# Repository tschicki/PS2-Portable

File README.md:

# A Custom PlayStation 2 Portable from Scratch

## About this Project
Just like the title says, this is a PlayStation 2 portable designed from scratch. This portable contains presumably world's first custom reverse engineered PS2 mainboard not made by Sony. It is only reusing 6 ICs of an original PS2, salvaged from SCPH-7900x or SCPH-9000x mainboards.

Most PS2 games can be played natively via OPL or NHDDL and the portable also features support for PS1 games via DKWDRV. Its two custom memory card slots are compatible with miniaturized PS2 Memory Cards, SD-Cards (MX4SIO) and a miniaturized SD2PSX.

Development of this project was started in 2022.

## Overview

### Custom PS2 AIO Mainboard
The mainboard was designed from scratch and is based on the SCPH-7900x and SCPH-9000x PS2 revisions. It also includes modern features, like USB-C PD charging and battery management, fully digital video output, I2S speaker and headphone amplifier and a customized boot ROM to boot directly into homebrew.  

#### Details:

- Battery Management:
    - USB C PD charging at 5V/9V/15V
    - Powered from 2S 5000mAh 21700 batteries for a total of 37Wh or about 4.5h of runtime on a single charge
    - Supports charge & play and includes a battery fuel gauge, protector and cell balancing

- Power Management:
    - Custom developed power management featuring modest EE and GS undervolting
    - Soft power button with minimal quiescent current
    - Monitoring to detect short circuits and overcurrent conditions

- Video Output:
    - Custom developed digital video processor based on a Trion T20 FPGA, written from scratch in VHDL
    - Fully digital direct drive of a 5” 480x800p DPI LCD by tapping right into the Graphics Synthesizer 24bit RGB output, replacing the stock PS2 video DAC
    - Features a motion-adaptive deinterlacer, line doubler, bilinear video scaler and OSD
    - Includes support for following resolutions:
        - 512i(256p) x 256, 512i(256p) x 320, 512i(256p) x 384, 512i(256p) x 448, 512i(256p) x 512, 512i(256p) x 640 at 50Hz
        - 448i(240p) x 256, 448i(240p) x 320, 448i(240p) x 384 at, 448i(240p) x 448, 448i(240p) x 512, 448i(240p) x 640 at 60Hz
        - VESA 480x640 at 60Hz

- Audio:
    - Custom I2S headphone and speaker amplifier using LM49450

- System Management:
    - Custom RP2040-based System Controller (SysCon) handling charging, discharging, power on/off, power management and monitoring
    - Custom developed DualShock 2 gamepad emulator running on core 1
        - Developed from scratch
        - Including rumble
        - Support for PS1 games
    - Custom developed configuration menu for changing and displaying various settings:
        - State of charge display (both in menu and via RGB LED)
        - EE temperature display and fan settings
        - Headphone and speaker volume
        - Various video processing settings, LCD brightness
        - Analog stick calibration and inversion
        - Deadzone settings
        - Power monitoring and TTE/TTF
        - And more…
    - SysCon firmware and video processor gateware updatable via drag & drop from USB-C

- Custom PS2 Boot ROM
    - Boots directly into PS2BBL, thanks to the BIOS modifications of Epaminondas – no softmods required

- Additional Features:
    - Fully functional PS2 RTC, enabled by an always-on standby rail

### Mechanical Assembly

The whole mechanical assembly was designed from scratch for FDM printing. The design goal was to make it as ergonomic as possible, while keeping the overall appearance simple and minimalistic.
The assembly is split into an outer shell and an inner assembly called 'skeleton' in an attempt to make assembly & disassembly easier and to allow easy shell replacements. Another priority for me was to use threaded inserts for all screws and to have easily replaceable non-soldered batteries.

#### Details:

- Gamepads
    - Custom designed & modular gamepad subassemblies that connect to the mainboard via I2C for best flexibility
    - PSVITA 2000 face buttons
    - 3.3V Nintendo Switch hall effect analog sticks
    - Rumble support: Coin-style rumble motors
    - Custom developed trigger mechanism using living hinges

- Cooling:
    - Custom designed aluminium heatsink covering the whole mainboard for maximum mechanical rigidity
    - Nintendo switch lite fan with configurable linear fan curve

- Interfaces:
    - Two fully accessible memory card slots, miniaturized by reusing SD card sockets
        - Natively compatible with MX4SIO, a custom reverse engineered PS2 memory card and a custom form factor SD2PSX 'uSD2PSX'
    - One USB A connector of the PS2, for using original accessories or USB sticks (DKWDRV)
    - Stereo headphone jack
    - USB-C connector for charging and SysCon firmware update

- Video and Audio
    - Stereo Nintendo Switch OLED speakers
    - 5" DPI LCD covered by a Nintendo 3DS XL glass screen lens

## Accessories
To further enhance the user experience, some more or less optional accessories were designed. 
- A *uSD2PSX* memory card in SD-Card format for running backups and saving games. Can also be unplugged to play on multiple consoles / portables, and is compatible for use on a stock console using a modified MX4SIO memory card. The best way to play games on the PS2 portable, and pretty much mandatory.
- A stand to place the portable while charging and when not in use.
- A travel case to protect the portable on-the-go.
- A reverse engineered PS2 memory card for saving games. Same form factor and interface as the uSD2PSX, but less useful. Don't bother with this and build the uSD2PSX instead.

## How to Build
I would highly recommend **not** to build one, even if you know what you are getting yourself into. If you're still not convinced to stop here, you can find the project documentation in the [documentation](https://github.com/tschicki/PS2-Portable/tree/main/Documentation) folder. It's best to read all the docs before you decide to continue.

You will need a lot of equipment and comprehensive electronics, soldering, troubleshooting and preferably also programming skills to have a chance of getting the custom PS2 mainboard to boot.

There is a [worklog](https://bitbuilt.net/forums/threads/some-ps2-project.5433/) of the whole project on BitBuilt, you might find some additional information there.

### Electronics
All custom PCBs, their Gerbers and their BOM can be found in the respective project under the [Electronics](https://github.com/tschicki/PS2-Portable/tree/main/Electronics) folder. All PCBs come from JLCPCB.

### Mechanics
All custom designed mechanical parts can be found under [Solidworks](https://github.com/tschicki/PS2-Portable/tree/main/Solidworks). If you would like to edit them, they were all designed using SolidWorks Maker. Otherwise, the STEP and STL exports can be found under [Output](https://github.com/tschicki/PS2-Portable/tree/main/Solidworks/Output).  
The housing parts were designed to be FDM printed, the CNC heatsink can be ordered from JLCCNC.

### Firmware & Gateware
The source files of the left & right gamepad firmware can be found [here](https://github.com/tschicki/PS2-Portable/tree/main/SysCon%20Firmware/PS2_Gamepad_02).  
The SysCon firmware can be found [here](https://github.com/tschicki/PS2-Portable/tree/main/SysCon%20Firmware/SysCon_FW).  
The Trion T20 gateware can be found [here](https://github.com/tschicki/PS2-Portable/tree/main/SysCon%20Firmware/SysCon_FW/ps2_video_processor).  

In order to obtain the required firmware, you need to compile it yourself. See the [documentation](https://github.com/tschicki/PS2-Portable/blob/main/Documentation/Part%2010_Development%20and%20Debugging.md) for that.

### Bill of Materials
The bill of materials for the mechanical assembly can be found [here](https://github.com/tschicki/PS2-Portable/blob/main/Documentation/Part%200_Mechanical%20BOM.md). The electrical BOM for each PCBA is in the [Electronics](https://github.com/tschicki/PS2-Portable/tree/main/Electronics) folder.

### Assembly Instructions
Check the [documentation](https://github.com/tschicki/PS2-Portable/tree/main/Documentation) folder. I tried to structure the sequence of documents so that it can guide you along for your build.

## Special Thanks
Thanks to the BitBuilt community for reading and commenting the worklog, it really helped to keep the motivation up! And special thanks to:
- Mister M and Gman for releasing their PS2 mainboard scans – without them this project would’ve taken much longer!
- Epaminondas for his amazing work on the custom PS2 BIOS. Seriously, you rock!
- Stuckpixel for helping out with converting the SPI part of the gamepad emulator to PIO. It’s much more reliable now!
- wisi and mixa232323 for guiding me in the right direction with all the boot ROM shenanigans
- StonedEdge and thedrew for their various suggestions and tips along the way
- All the awesome people working on the SD2PSX, neutrino and NHDDL! It's incredible to see how far the PS2 homebrew scene has come in the last couple of years!

## Known Bugs and Anomalies
This is a hobby project, so the end result will never be flawless. The design has seen hundreds of hours of playtesting, where following anomalies were discovered:
- The PS2 RTC drifts by about 7s a day, this could most likely be solved by selecting a different 32kHz crystal or by tweaking the load capacitors. However, the characteristics of the original crystal and the Mechacon's oscillator circuits are unknown.
- Games with static and permanently flickering elements can cause image retention on the LCD. I only noticed this on one game so far - Castlevania: Symphony of the Night, where certain HUD elements flicker. It is not recommended to play such games to prevent damage to the LCD.

## License
All firmware, gateware and hardware in this repository is licensed under the [MIT License](LICENSE).

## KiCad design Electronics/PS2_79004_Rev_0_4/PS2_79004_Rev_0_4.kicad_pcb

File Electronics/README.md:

# PCB Outputs

This directory contains all the PCB projects. You will find the Gerber files in the respective *Gerber/* folders. The BOM is in ibom format and can be found in the *BOM/* folders where applicable. For very simple PCBs like the gamepad flex PCBs you will find the needed components in Part 5 of the project documentation.

If you need the BOM in CSV format, you can open the ibom files and export the content as CSV.

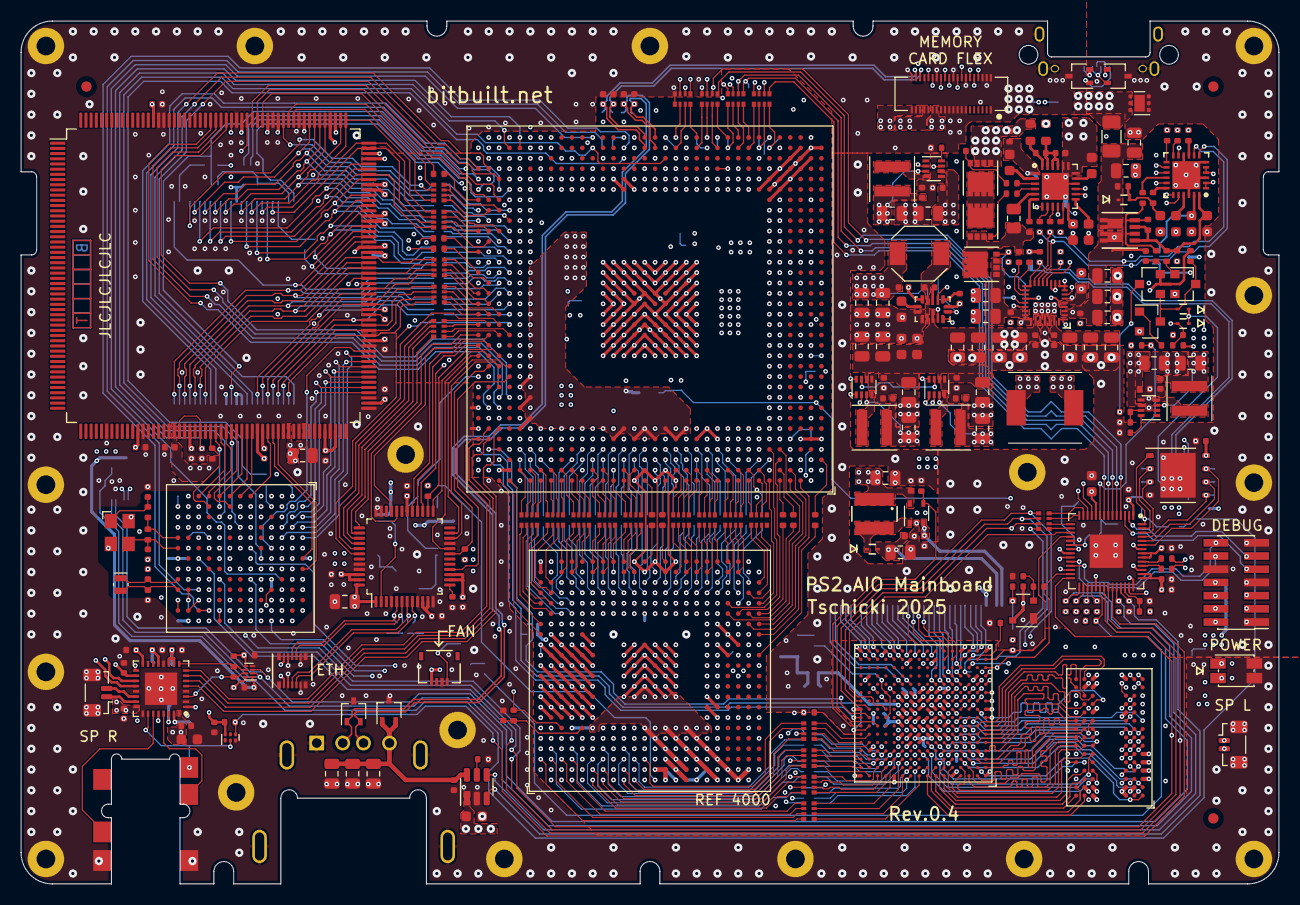
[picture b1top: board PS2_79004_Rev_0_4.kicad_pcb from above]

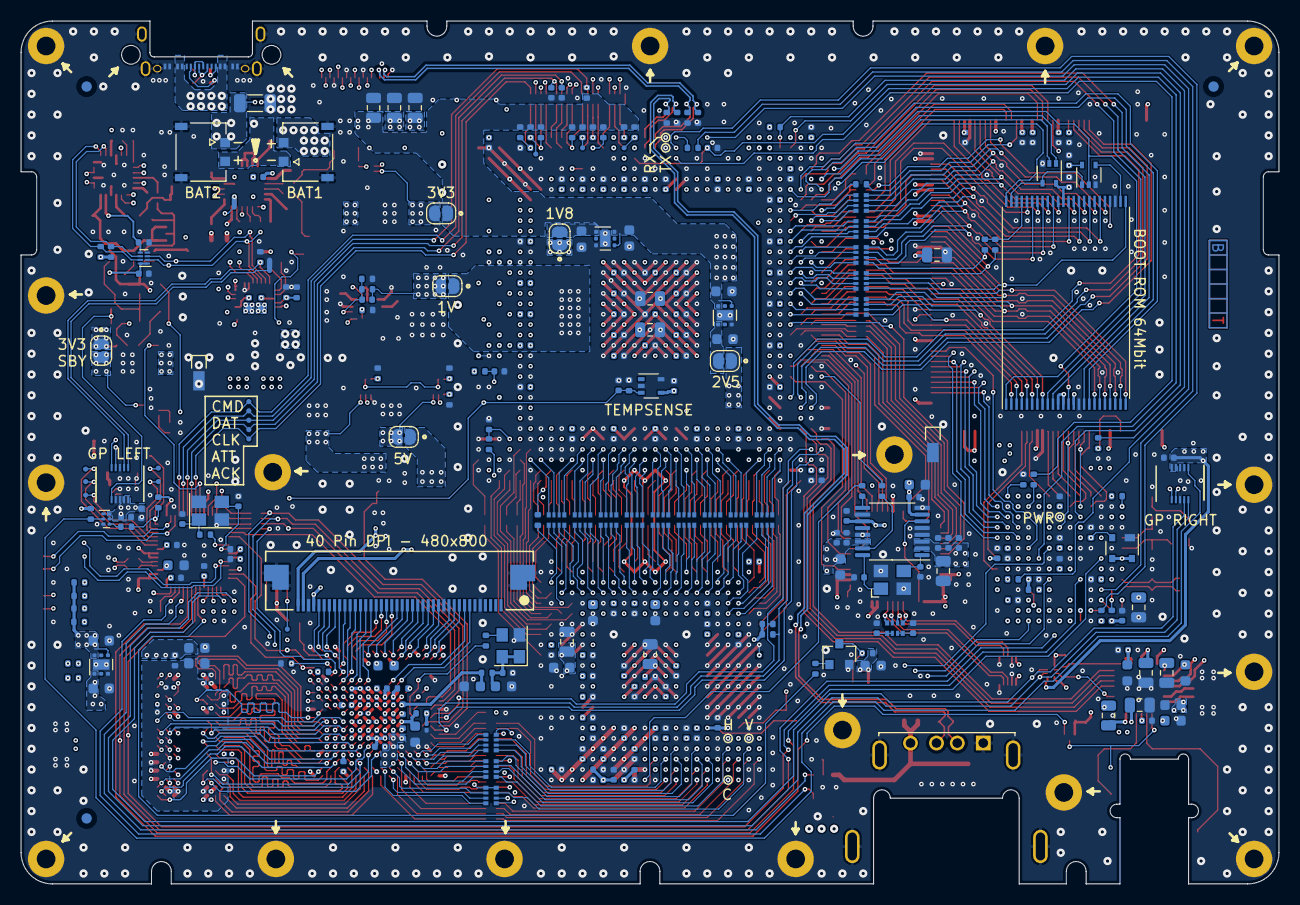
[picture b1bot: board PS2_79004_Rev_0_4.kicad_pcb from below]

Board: 6 copper layers, 121.0 x 83.0 mm, 770 parts (488 on the bottom side), 807 nets.

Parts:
C201, C202, C1402, C2002, C2003, C2105, C2106, C2112, C2504: 2u2; C_0805_2012Metric
C203, C204, C205, C206, C605, C616, C806, C809, C2107, C2114, C2115, C2118, C2119, C2202, C2205, C2208: 1u; C_0603_1608Metric
C207, C208, C306, C309, C314, C318, C325, C328, C401, C510, C511, C512, C513, C516, C517, C518, C519, C532, C601, C602, C606, C607, C608, C609, C610, C611, C612, C613, C614, C615, C801, C805, C810, C901, C905, C906, C907, C908, C909, C910, C911, C912, C913, C914, C916, C917, C918, C919, C920, C921, C922, C923, C924, C925, C926, C927, C928, C929, C930, C931, C932, C933, C934, C935, C936, C937, C938, C939, C944, C1301, C1401, C1403, C1404, C1405, C1406, C1407, C1408, C1409, C1503, C1504, C1507, C1601, C1602, C1701, C1702, C1802, C1803, C1804, C1805, C1806, C1807, C1808, C1809, C1810, C1811, C1813, C1814, C1815, C1816, C1817, C1818, C2001, C2004, C2005, C2006, C2007, C2008, C2101, C2102, C2104, C2108, C2109, C2110, C2111, C2113, C2116, C2117, C2201, C2203, C2204, C2206, C2207, C2209, C2210, C2213, C2215, C2216, C2217, C2218, C2219, C2220, C2221, C2222, C2223, C2224, C2225, C2226, C2227, C2229, C2230, C2231, C2232, C2233, C2234, C2235, C2236, C2237, C2502, C2903, C3005, C3006: 100n; C_0402_1005Metric
C301, C302, C303, C304, C305, C307, C316, C319, C320, C321, C322, C323, C501, C502, C1801, C1812, C2103, C2501: 10u; C_0805_2012Metric
C308, C503, C506, C509, C528, C529, C530, C531, C534, C535, C538, C2601, C2608, C2801, C2814, C3004: 4u7; C_0603_1608Metric
C310, C311: 47n; C_0402_1005Metric
C312, C315, C317, C324, C2901, C2902: 470n; C_0603_1608Metric
C313, C803, C808, C811, C1303, C2212, C2228, C2301, C2503: 1n; C_0402_1005Metric
C326, C327, C525, C807, C902, C903, C904, C915, C940: 10n; C_0402_1005Metric
C504, C505, C507, C508, C521, C522, C523, C524, C533, C536, C537, C942, C943, C2211, C2214, C3001, C3002, C3003: 22u; C_0805_2012Metric
C514, C2602, C2618, C2625, C2626, C2627, C2628: 220n; C_0402_1005Metric
C515: 22n; C_0402_1005Metric
C520: 270p; C_0402_1005Metric
C526, C527: 47u; C_0805_2012Metric
C603, C604, C1501, C1502, C1505, C1506: 15p; C_0402_1005Metric
C802, C804, C1302: 5p; C_0402_1005Metric
C941, C2401, C2402, C2403, C2404, C2405, C2406, C2407: 100p; C_0402_1005Metric
C2603, C2604, C2605, C2606, C2607, C2609, C2610, C2611, C2612, C2613, C2614, C2615, C2616, C2617, C2619, C2620, C2621, C2622, C2623, C2624, C2802, C2803, C2804, C2805, C2806, C2807, C2808, C2809, C2810, C2811, C2812, C2813: 100n; C_0201_0603Metric
D201, D202, D3001, D3002: ESDA25W; SOT-323_SC-70
D203, D401, D402, D2501: D_Schottky; SOD-923_0P6X0P85_ONS
D1501: Power LED; LED_Lite-ON_LTST-C155
F201: Fuse; Fuse_1206_3216Metric
FB2601, FB2801, FB2901: 33R @ 100MHz; R_0402_1005Metric
FID3001, FID3002, FID3003, FID3004, FID3005, FID3006: Fiducial; Fiducial_1mm_Mask2mm
J301: BAT1; MOLEX_2082940020_2pin
J302: BAT2; MOLEX_2082940020_2pin
J2101: LEFT SPEAKER; JST_SUR_BM02B-SURS-TF_1x02-1MP_P0.80mm_Vertical
J2102: RIGHT SPEAKER; JST_SUR_BM02B-SURS-TF_1x02-1MP_P0.80mm_Vertical
J2103: SJ-43504-SMT-TR; CUI_SJ-43504-SMT-TR
J2501: Conn_01x40_MountingPin; CONN_62684402100ALF_AMP
J3001: EXPANSION HDR; DF40C-40DS-0.4V
J3002: ETH; DF40C-10DP-0.4V51_HIR
J3003: USB_A; PS2_USB_mid_mount
J3004: GAMEPAD LEFT; DF40C-10DS-0.4V51_HIR
J3005: GAMEPAD RIGHT; DF40C-10DS-0.4V51_HIR
J3006: Debug; FTSH-107-01-F-DV-K-P-TR
J3007: 2328702-4; TE_2328702-4
JP501, JP502, JP503, JP504, JP505, JP506: Jumper_2_Bridged; SolderJumper-2_P1.3mm_Open_RoundedPad1.0x1.5mm
L301: 1uH; L_TDK_SPM6530
L501, L502, L503, L504: 2u2; L_Coilcraft_XGL4020
L505: 1u; SPM5030T-1R0M
L2501: 4u7; IND_TAIYO_NRS4012_TAY
NT301, NT302: NetTie_2; NetTie-2_SMD_Pad0.5mm
P201: CX90MW6-16P; CX90_632x232_HIR
Q201: Q_SI7223DN; PowerPAK1212-8_VIS
Q301, Q302, Q303: CSD17575Q3; CSD17308Q3
Q401, Q402, Q601: DMN67D8L; SOT-23
Q403: BSS84AK; SOT-23
R201, R1701, R1702: 560R; R_0402_1005Metric
R202, R205, R311, R313, R406, R604, R606, R614, R616, R1304, R1305, R1307, R1504, R1505, R1507, R1508, R1510, R2001, R2307, R2401, R2402, R2403, R2404, R2405, R2406, R2408, R2409, R2411, R2412: 1k; R_0402_1005Metric
R203, R206, R207, R211, R309, R401, R404, R507, R607, R610, R2101: 100k; R_0402_1005Metric
R204, R509, R2407, R2410, R2413, R2414: 15k; R_0402_1005Metric
R208, R209, R301, R601, R608, R609, R611, R612, R613, R2103, R2104: 2k2; R_0402_1005Metric
R210, R306: 100R; R_0402_1005Metric
R302, R303, R2902: 12k; R_0402_1005Metric
R304, R305, R314, R315, R1301, R1302, R1303, R1306, R1509, R2301, R2302, R2303, R2304, R2305, R2306, R2308: 68R; R_0402_1005Metric
R307: 30k; R_0402_1005Metric
R308: 5k23; R_0402_1005Metric
R310: 270R; R_0805_2012Metric
R312: 0R01; R_1206_3216Metric
R316: 10R; R_0402_1005Metric
R317, R318: 68R; R_0603_1608Metric
R402, R403, R405, R407, R501, R508, R605, R615, R1201, R1202, R1501, R1502, R1503, R1514, R1601, R2102, R2501, R2701, R2702, R2703, R2704, R2705, R2706, R2707, R2708, R2709, R2710, R2711: 10k; R_0402_1005Metric
R502, R503, R504, R505: 42k2; R_0402_1005Metric
R506: 6k8; R_0402_1005Metric
R510, R1512, R1515: 45k3; R_0402_1005Metric
R602, R603, R801, R802, R1506, R2901: 22R; R_0402_1005Metric
R1511: 1M; R_0402_1005Metric
R1513, R2002: 1K5; R_0402_1005Metric
R2003: 1K2; R_0402_1005Metric
R2502: 5R6; R_0402_1005Metric
RN601, RN1301, RN1302, RN1303, RN1304, RN1305, RN1306, RN1307, RN1308, RN1309, RN2001, RN2301, RN2302, RN2303, RN2304, RN2305, RN2306, RN2307, RN2308, RN2309, RN2310, RN2311, RN2312, RN2313, RN2314, RN2315, RN2316, RN2317, RN2318, RN2319, RN2320, RN2321, RN2322, RN2323, RN2324, RN2325, RN2401, RN2402, RN2403, RN2404: 68R; R_Array_Convex_4x0402
RN2002: 51R; R_Array_Convex_4x0402
TP201, TP202, TP203, TP204, TP205, TP206, TP301, TP302, TP303, TP304, TP305, TP306, TP601, TP602, TP603, TP604, TP605, TP606, TP607, TP608, TP1101, TP1301, TP1302, TP1303, TP1304, TP1305, TP1306, TP1307, TP1308, TP1309, TP1310, TP1311, TP1312, TP1313, TP1314, TP1315, TP1316, TP1317, TP1318, TP1319, TP1320, TP1321, TP1322, TP1323, TP1324, TP1325, TP1326, TP1327, TP1328, TP1329, TP1501, TP1502, TP1503, TP1504, TP1505, TP1506, TP1507, TP1508, TP1509, TP1510, TP1511, TP1512, TP1513, TP1514, TP1515, TP1516, TP1517, TP1518, TP1519, TP1520, TP1521, TP1522, TP1523, TP1524, TP1525, TP1526, TP1527, TP1528, TP1529, TP1530, TP1531, TP1532, TP1533, TP1534, TP1535, TP1536, TP1537, TP1538, TP1539, TP1540, TP1541, TP1542, TP1543, TP1544, TP1545, TP1546, TP1547, TP1548, TP1701, TP1702, TP1703, TP1704, TP1901, TP2301, TP2302, TP2303, TP2304, TP2305, TP2306, TP2307, TP2308, TP2309, TP2310, TP2311, TP2312, TP2313, TP2314, TP2315, TP2316, TP2317, TP2318, TP2319, TP2320, TP2321, TP2322, TP2323, TP2324, TP2325, TP2326, TP2327, TP2328, TP2329, TP2330, TP2331, TP2332, TP2333, TP2334, TP2335, TP2401, TP2402, TP2403, TP2404, TP2405, TP2406, TP2407, TP2408, TP2409, TP2410, TP2411, TP2412, TP2701, TP2702, TP2703, TP2704, TP2705, TP2706, TP2707, TP2708, TP2709, TP2901, TP2902, TP2903, TP2904, TP2905, TP2906: Solder_Point; Solder_Point_127
TP3001, TP3002, TP3003, TP3004, TP3005, TP3006, TP3007, TP3008, TP3009, TP3010, TP3011, TP3012, TP3013, TP3014, TP3015, TP3016, TP3017: Solder_Point; mounting_hole_1.6mm
TP3018, TP3019: Solder_Point; TE_1551576-5
U201: TVS2200DRV; WSON-6-1EP_2x2mm_P0.65mm_EP1x1.6mm
U202: STUSB4500; QFN-24_EP_4x4_Pitch0.5mm
U203, U2101: TXS0102DQE; X2SON-8_1.4x1mm_P0.35mm
U301: BQ25792B; BQ25792RQMR
U302: MAX17320; TQFN-24-1EP_4x4mm_P0.5mm_EP2.6x2.6mm
U501: MPQ8626GD; MPQ8626GD-Z
U502, U503, U504, U505: TPS629210; SOT-583
U506: AP22653A; SOT-23-6
U507: TLV75525PDRV; WSON-6-1EP_2x2mm_P0.65mm_EP1x1.6mm
U508, U509: TLV75518PDRV; WSON-6-1EP_2x2mm_P0.65mm_EP1x1.6mm
U601, U2102: 74LVC1G07; Texas_USON-6_1x1.45mm_P0.5mm_SMD
U602: W25Q128JVPIQ; WSON-8-1EP_6x5mm_P1.27mm_EP3.4x4.3mm
U603: RP2040; QFN-56-1EP_7x7mm_P0.4mm_EP3.2x3.2mm
U801: 627G04LF; TSSOP-16_4.4x5mm_P0.65mm
U901: CXD2976GB; PS2_CXD2976GB_35.0x35.0mm_P1.0mm
U1401: CXR726080; BGA-169_14.0x14.0mm_Layout13x13_P1.0mm
U1501, U2701: APX811-31UG; SOT-143
U1601: LM20BIM7; SOT-353_SC-70-5
U1701, U1702: 74LVC1G08; SOT-353_SC-70-5
U1703: S29JL064J55TFI000; TSOP-I-48_18.4x12mm_P0.5mm
U1801: CXD3098AQ; PS2_CXD3098AQ_208_28x28mm_P0.5mm
U2001: BCM5241; LQFP-48_7x7mm_P0.5mm
U2103: LM49450; WQFN-32-1EP_5x5mm_P0.5mm_EP3.1x3.1mm
U2201: CXD2980; PS2_CXD2980CGB_23.0x23.0mm_P1.0mm
U2501: TPS92360; SOT-353_SC-70-5
U2601: T20F256I4; BGA-256_14.0x14.0mm_Layout16x16_P0.8mm_Ball0.45mm_Pad0.32mm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
U2801: IS45S32400F; BGA-90_8.0x13.0mm_Layout2x3x15_P0.8mm
X2901: ASE-50MHz; Oscillator_SMD_Abracon_ASE-4Pin_3.2x2.5mm
Y601: 12MHz; Crystal_SMD_3225-4Pin_3.2x2.5mm
Y801: 18.432MHz; Crystal_SMD_3225-4Pin_3.2x2.5mm
Y1501: 32.768kHz; Crystal_SMD_MicroCrystal_CM9V-T1A-2Pin_1.6x1.0mm
Y1502: 16,934MHz; Crystal_SMD_3225-4Pin_3.2x2.5mm

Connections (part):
1V2_T20: C516.1, C521.1, C2601.1, C2602.1, C2603.1, C2604.1, C2605.1, C2606.1, C2607.1, C2609.1, C2611.1, FB2601.1, L501.2, U502.3 (VOS), U2601.E9 (VCC), U2601.F8 (VCC), U2601.F9 (VCC), U2601.J6 (VCC), U2601.J7 (VCC), U2601.K9 (VCC)
1V8_PS2: C809.1, C810.1, C811.1, C906.1, C908.1, C910.1, C912.1, C915.1, C918.1, C921.1, C923.1, C925.1, C927.1, C929.1, C1407.2, C1408.2, C1409.2, C1812.1, C1813.1, C1814.1, C1815.1, C1816.1, C1817.1, C1818.1, C2221.1, C2223.1, C2225.1, C2227.1, C2229.1, C2230.1, C2231.1, C2232.1, C2233.1, C2234.1, C2235.1, C2236.1, C2237.1, JP506.2 (B), U801.7 (1V8), U801.11 (1V8), U901.AA5 (1V8), U901.AB6 (1V8), U901.AB30 (1V8), U901.AC5 (1V8), U901.AC29 (1V8), U901.AD6 (1V8), U901.AD30 (1V8), U901.AE5 (1V8), U901.AE29 (1V8), U901.AF6 (1V8), U901.AF30 (1V8), U901.AG5 (1V8), U901.AG29 (1V8), U901.AH30 (1V8), U901.AJ21 (1V8), U901.AJ23 (1V8), U901.AJ25 (1V8), U901.AJ27 (1V8), U901.AJ29 (1V8), U901.AK22 (1V8), U901.AK24 (1V8), U901.AK26 (1V8), U901.AK28 (1V8), U901.AK30 (1V8), U901.AL31 (1V8), U901.AM32 (1V8), U901.AN33 (1V8), U901.B2 (1V8), U901.C3 (1V8), U901.D4 (1V8), U901.E5 (1V8), U901.E7 (1V8), U901.E9 (1V8), U901.E11 (1V8), U901.E13 (1V8), U901.F6 (1V8), U901.F8 (1V8), U901.F10 (1V8), U901.F12 (1V8), U901.G5 (1V8), U901.H6 (1V8)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
1V8_T20: C538.1, C2616.1, C2623.1, C2628.1, U509.1 (OUT), U2601.E10 (VCCIO3A_3B_3C), U2601.F10 (VCCIO3A_3B_3C), U2601.F11 (VCCIO3A_3B_3C)
1V_PS2: C913.1, C916.1, C919.1, C922.1, C924.1, C926.1, C928.1, C930.1, C931.1, C932.1, C933.1, C934.1, C935.1, C936.1, C937.1, C938.1, C939.1, C940.1, C941.1, C942.1, C943.1, C944.1, C2201.1, C2202.1, C2204.1, C2205.1, C2207.1, C2208.1, C2210.1, C2211.1, C2213.1, C2214.1, C2216.1, C2218.1, C2220.1, C2222.1, C2224.1, C2226.1, C2228.1, JP501.2 (B), U901.AA14 (1V25), U901.AA16 (1V25), U901.AA18 (1V25), U901.AA20 (1V25), U901.AA22 (1V25), U901.AB13 (1V25), U901.AB15 (1V25), U901.AB17 (1V25), U901.AB19 (1V25), U901.AB21 (1V25), U901.AJ9 (1V25), U901.AJ11 (1V25), U901.AJ13 (1V25), U901.AJ15 (1V25), U901.AJ17 (1V25), U901.AJ19 (1V25), U901.AK8 (1V25), U901.AK10 (1V25), U901.AK12 (1V25), U901.AK14 (1V25), U901.AK16 (1V25), U901.AK18 (1V25), U901.AK20 (1V25), U901.B34 (1V25), U901.N14 (1V25), U901.N16 (1V25), U901.N18 (1V25), U901.N20 (1V25), U901.N22 (1V25), U901.P13 (1V25), U901.P15 (1V25), U901.P17 (1V25), U901.P19 (1V25), U901.P21 (1V25), U901.R14 (1V25), U901.R16 (1V25), U901.R18 (1V25), U901.R20 (1V25), U901.R22 (1V25), U901.T13 (1V25), U901.T15 (1V25)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
2V5_PS2: C914.1, C917.1, C920.1, C2116.1, C2117.1, C2118.1, C2119.1, C2203.1, C2206.1, C2209.1, C2212.1, JP505.2 (B), U901.AP2 (2V5), U901.AP33 (2V5), U901.B33 (2V5), U2103.28 (HPVDD), U2103.32 (CPVDD), U2201.A21 (2V5), U2201.T1 (2V5)
3V3_PS2: C529.1, C530.1, C801.1, C803.1, C805.1, C806.1, C807.1, C808.1, C901.1, C902.1, C903.1, C904.1, C905.1, C907.1, C909.1, C911.1, C1403.1, C1404.1, C1405.1, C1406.1, C1507.1, C1601.1, C1701.1, C1702.1, C1801.1, C1802.1, C1803.1, C1804.1, C1805.1, C1806.1, C1807.1, C1808.1, C1809.1, C1810.1, C1811.1, C2002.1, C2004.1, C2005.1, C2006.1, C2102.1, C2107.1, C2108.1, C2109.1, C2215.1, C2217.1, C2219.1, C3003.1, J3001.27, J3001.29, J3002.9, J3002.10, JP504.2 (B), R1201.1, R1202.1, R1304.2, R1501.1, R1503.1, R1512.1, R1515.1, R2001.1, R2002.1, R2101.2, R2102.1, R2103.1, R2104.1, R2401.1, R2402.1, R2403.1, R2404.1, R2405.1, R2406.1, R2408.1, R2409.1, R2411.1, R2412.1, U507.4 (EN), U507.6 (IN), U508.4 (EN), U508.6 (IN), U801.2 (3V5), U801.3 (3V5)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
3V3_SBY: C208.2, C601.1, C602.1, C608.1, C609.1, C610.1, C611.1, C612.1, C614.1, C615.1, C616.1, C2101.2, C3002.1, C3005.1, C3006.1, J3001.31, J3001.33, J3004.8, J3004.10, J3005.8, J3005.10, JP503.2 (B), R208.1, R209.1, R301.2, R407.1, R601.1, R605.1, R608.1, R609.1, R610.2, R611.1, R612.1, R613.1, U203.1 (VCCA), U203.8 (VCCB), U601.6 (VCC), U602.8 (VCC), U603.1 (IOVDD), U603.10 (IOVDD), U603.22 (IOVDD), U603.33 (IOVDD), U603.42 (IOVDD), U603.43 (ADC_AVDD), U603.44 (VREG_IN), U603.48 (USB_VDD), U603.49 (IOVDD), U2101.1 (VCCA)
3V3_T20: C517.1, C522.1, C531.1, C2612.1, C2613.1, C2614.1, C2615.1, C2617.1, C2618.1, C2619.1, C2620.1, C2621.1, C2622.1, C2624.1, C2625.1, C2626.1, C2627.1, C2801.1, C2802.1, C2803.1, C2804.1, C2805.1, C2901.1, FB2801.1, FB2901.1, J2501.37, JP504.1 (A), L502.2, R2702.1, R2703.1, R2704.2, R2705.2, R2706.2, R2707.2, R2708.2, R2711.1, U503.3 (VOS), U509.4 (EN), U509.6 (IN), U2601.F6 (VCCIO1D_1E), U2601.G6 (VCCIO1D_1E), U2601.H6 (VCCIO1B_1C), U2601.H7 (VCCIO1B_1C), U2601.J10 (VCCIO3D_3E), U2601.J11 (VCCIO3D_3E), U2601.K6 (VCCIO1A), U2601.L6 (VCCIO4B), U2601.L7 (VCCIO4B), U2601.L10 (VCCIO4A), U2601.L11 (VCCIO4A), U2701.4 (VCC), U2801.A7 (VDD), U2801.F9 (VDD), U2801.L7 (VDD), U2801.R7 (VDD)
5V: C528.1, C2110.1, C2111.1, C2113.1, C2114.1, C2115.1, C2501.2, C2502.1, C3001.1, C3004.1, J3001.35, J3001.37, J3001.39, J3007.1, JP502.2 (B), L2501.1, R615.1, U506.1 (IN), U2103.16 (VDD), U2103.18 (LSVDD), U2103.24 (LSVDD), U2501.5 (VIN)
5V_USB: C532.1, C533.1, C536.1, C537.1, D3001.1 (K), D3001.2 (K), J3003.1 (VBUS), U506.6 (OUT)
+1V1: C605.1, C606.1, C607.1, U603.23 (DVDD), U603.45 (VREG_VOUT), U603.50 (DVDD)
/Battery Management/BAT_CENT: J301.1, J302.2, R318.2
/Battery Management/BAT_POS: C328.1, J301.2, Q303.1 (S), Q303.2 (S), Q303.3 (S), R316.2, R317.2
/Battery Management/BQ_BAT: C318.2, C320.2, C322.2, Q301.1 (S), Q301.2 (S), Q301.3 (S), U301.22 (BAT), U301.23 (BAT)
/Battery Management/ILIM: R309.1, U301.17 (ILIM_HIZ)
/Battery Management/PROG: R302.2, R303.2, U301.20 (PROG)
/Battery Management/REGN: C308.2, R308.2, R309.2, U301.5 (REGN)
/Battery Management/SW1: C310.2, L301.1, U301.28 (SW1)
/Battery Management/SW2: C311.2, L301.2, U301.26 (SW2)
/Battery Management/SYS_I2C_SCL: R304.1, R612.2, U203.2 (A1), U301.14 (SCL), U603.32 (GPIO21)
/Battery Management/SYS_I2C_SDA: R305.1, R611.2, U203.3 (A2), U301.15 (SDA), U603.31 (GPIO20)
/Battery Management/VBUS: C207.2, C302.2, C304.2, C307.2, C309.2, Q201.7 (D), Q201.8 (G), R205.2, U301.2 (VBUS), U301.3 (VBUS), U301.8 (VAC2), U301.9 (VAC1)
/Battery Management/VPACK+: Q301.5-8 (D), Q302.1 (S), Q302.2 (S), Q302.3 (S), R306.2, R310.1, R311.2
/Battery Management/VSYS: C314.2, C316.2, C319.2, C321.2, C323.2, C501.1, C502.1, C504.1, C505.1, C506.1, C507.1, C508.1, C509.1, C510.1, C511.1, C512.1, C513.1, Q403.2 (S), R403.2, U301.25 (SYS), U501.3 (VIN), U502.6 (VIN), U503.6 (VIN), U504.6 (VIN), U505.6 (VIN)
/Battery Management/~CHRG_EN: R301.1, U301.13 (~CE), U603.12 (GPIO9)
/Connectors/MC1_ACK: J3001.32, RN2401.2 (R2.1)
/Connectors/MC1_ATT: J3001.26, RN2401.4 (R4.1)
/Connectors/MC1_CLK: J3001.30, RN2401.3 (R3.1)
/Connectors/MC1_CMD: J3001.24, RN2402.3 (R3.1)
/Connectors/MC1_DAT: J3001.22, RN2402.4 (R4.1)
/Connectors/MC2_ACK: J3001.18, RN2404.3 (R3.1)
/Connectors/MC2_ATT: J3001.12, RN2403.1 (R1.1)
/Connectors/MC2_CLK: J3001.16, RN2404.4 (R4.1)
/Connectors/MC2_CMD: J3001.10, RN2403.2 (R2.1)
/Connectors/MC2_DAT: J3001.8, RN2403.3 (R3.1)
/Connectors/RD+: J3002.3, RN2002.8 (R1.2), U2001.8 (RD+)
/Connectors/RD-: J3002.5, RN2002.7 (R2.2), U2001.7 (RD-)
/Connectors/SPI_SS: J3006.5, R2701.1, U2601.P3 (GPIOL_00_SS_N)
/Connectors/SYS_FAN_PWM: J3007.4, Q601.3 (D), R615.2
/Connectors/SYS_SWCLK: J3006.12, U603.24 (SWCLK)
/Connectors/SYS_SWDIO: J3006.14, U603.25 (SWD)
/Connectors/SYS_UART_RX: J3006.9, U603.3 (GPIO1)
/Connectors/SYS_UART_TX: J3006.11, U603.2 (GPIO0)
/Connectors/TCK: J3006.4, R2706.1, U2601.M2 (TCK)
/Connectors/TD+: J3002.6, RN2002.5 (R4.2), U2001.5 (TD+)
/Connectors/TD-: J3002.4, RN2002.6 (R3.2), U2001.6 (TD-)
/Connectors/TDI: J3006.8, R2704.1, U2601.K5 (TDI)
/Connectors/TDO: J3006.6, R2705.1, U2601.L5 (TDO)
/Connectors/TMS: J3006.2, R2707.1, U2601.M1 (TMS)
/Connectors/USB1_DN: C2406.1, D3002.2 (K), J3003.2 (D-), R2413.1, U901.AN17 (USB1_D-)
/Connectors/USB1_DP: C2407.1, D3002.1 (K), J3003.3 (D+), R2414.1, U901.AP17 (USB1_D+)
/Connectors/USB2_DN: C2404.1, J3001.38, R2407.1, U901.AN18 (USB2_D-)
/Connectors/USB2_DP: C2405.1, J3001.36, R2410.1, U901.AP18 (USB2_D+)
/Connectors/~SYSCON_BOOTSEL: J3005.2, R601.2, U601.2
/PS2_REG_EN: R607.1, U501.5 (EN), U502.7 (EN), U503.7 (EN), U504.7 (EN), U506.3 (EN), U603.39 (GPIO27_ADC1)
/PS2_REG_PG: R610.1, U501.9 (PGOOD), U502.2 (PG), U503.2 (PG), U504.2 (PG), U506.4 (~FAULT), U603.38 (GPIO26_ADC0)
/PlayStation 2 - MAIN/AUX_I2C_SCL: J3004.3, J3005.3, R609.2, U603.30 (GPIO19), U2101.3 (A2)
/PlayStation 2 - MAIN/AUX_I2C_SDA: J3004.1, J3005.1, R608.2, U603.29 (GPIO18), U2101.2 (A1)
/PlayStation 2 - MAIN/Audio & Network/AUDIO_MC: U901.E34 (AUDIO_MC), U2103.8 (MCLK)
/PlayStation 2 - MAIN/Audio & Network/AUDIO_SCL: U901.F33 (AUDIO_SCL), U2103.7 (I2S_CLK)
/PlayStation 2 - MAIN/Audio & Network/AUDIO_SDA: U901.E33 (AUDIO_SDA), U2103.6 (I2S_SDI)
/PlayStation 2 - MAIN/Audio & Network/AUDIO_WS: U901.F32 (AUDIO_WS), U2103.5 (I2S_WS)
/PlayStation 2 - MAIN/Audio & Network/Ethernet_16: U901.L31 (ETH_16), U2001.16 (EE_L31)
/PlayStation 2 - MAIN/Audio & Network/Ethernet_19: R2002.2, U901.M33 (ETH_19), U2001.19 (EE_M33)
/PlayStation 2 - MAIN/Audio & Network/Ethernet_20: U901.N34 (ETH_20), U2001.20 (EE_N34)
/PlayStation 2 - MAIN/Audio & Network/Ethernet_22: U901.M32 (ETH_22), U2001.22 (EE_M32)
/PlayStation 2 - MAIN/Audio & Network/Ethernet_23: U901.M31 (ETH_23), U2001.23 (EE_M31)
/PlayStation 2 - MAIN/Audio & Network/Ethernet_25: U901.N33 (ETH_25), U2001.25 (EE_N33)
/PlayStation 2 - MAIN/Audio & Network/Ethernet_26: R2001.2, U901.N32 (ETH_26), U2001.26 (EE_N32)
/PlayStation 2 - MAIN/Audio & Network/Ethernet_27: U901.N31 (ETH_27), U2001.27 (EE_N31)
/PlayStation 2 - MAIN/Audio & Network/Ethernet_28: U901.P34 (ETH_28), U2001.28 (EE_P34)
/PlayStation 2 - MAIN/Audio & Network/Ethernet_29: U901.P33 (ETH_29), U2001.29 (EE_P33)
/PlayStation 2 - MAIN/Audio & Network/Ethernet_32: U901.R34 (ETH_32), U2001.32 (EE_R34)
/PlayStation 2 - MAIN/Audio & Network/Ethernet_33: U901.R33 (ETH_33), U2001.33 (EE_R33)
/PlayStation 2 - MAIN/Audio & Network/Ethernet_37: RN2001.5 (R4.2), U901.R32 (ETH_37)
/PlayStation 2 - MAIN/Audio & Network/Ethernet_38: RN2001.6 (R3.2), U901.R31 (ETH_38)
/PlayStation 2 - MAIN/Audio & Network/Ethernet_39: RN2001.7 (R2.2), U901.T34 (ETH_39)
/PlayStation 2 - MAIN/Audio & Network/Ethernet_40: RN2001.8 (R1.2), U901.T33 (ETH_40)
/PlayStation 2 - MAIN/Audio & Network/Ethernet_41: U901.T32 (ETH_41), U2001.41 (EE_T32)
/PlayStation 2 - MAIN/Audio & Network/Ethernet_42: U901.T31 (ETH_42), U2001.42 (EE_T31)
/PlayStation 2 - MAIN/Audio/BYPASS: C2106.1, U2103.17 (BYPASS)
/PlayStation 2 - MAIN/Audio/C1N: C2105.2, U2103.31 (C1N)
/PlayStation 2 - MAIN/Audio/C1P: C2105.1, U2103.1 (C1P)
/PlayStation 2 - MAIN/Audio/HPL: J2103.2, U2103.29 (HPL)
/PlayStation 2 - MAIN/Audio/HPR: J2103.3, U2103.27 (HPR)
/PlayStation 2 - MAIN/Audio/HP_SENSE: J2103.5, U2102.2, U2103.26 (HPS)
/PlayStation 2 - MAIN/Audio/LS+: J2101.1, U2103.19 (LLS+)
/PlayStation 2 - MAIN/Audio/LS-: J2101.2, U2103.20 (LLS-)
/PlayStation 2 - MAIN/Audio/REF: C2103.1, C2104.1, U2103.13 (REF)
/PlayStation 2 - MAIN/Audio/RS+: J2102.1, U2103.23 (RLS+)
/PlayStation 2 - MAIN/Audio/RS-: J2102.2, U2103.22 (RLS-)
/PlayStation 2 - MAIN/BIOS/A0: R1701.2, RN1304.4 (R4.1), U1801.140 (HA00)
/PlayStation 2 - MAIN/BIOS/A1: RN1304.3 (R3.1), U1703.25 (A0), U1801.139 (HA01)
/PlayStation 2 - MAIN/BIOS/A2: RN1304.2 (R2.1), U1703.24 (A1), U1801.138 (HA02)
/PlayStation 2 - MAIN/BIOS/A3: RN1304.1 (R1.1), U1703.23 (A2), U1801.137 (HA03)
/PlayStation 2 - MAIN/BIOS/A4: RN1303.5 (R4.2), U1703.22 (A3), U1801.134 (HA04)
/PlayStation 2 - MAIN/BIOS/A5: RN1301.4 (R4.1), U1703.21 (A4), U1801.133 (HA05)
/PlayStation 2 - MAIN/BIOS/A6: RN1301.3 (R3.1), U1703.20 (A5), U1801.132 (HA06)
/PlayStation 2 - MAIN/BIOS/A7: RN1303.6 (R3.2), U1703.19 (A6), U1801.131 (HA07)
/PlayStation 2 - MAIN/BIOS/A8: RN1303.7 (R2.2), U1703.18 (A7), U1801.128 (HA08)
/PlayStation 2 - MAIN/BIOS/A9: RN1301.2 (R2.1), U1703.8 (A8), U1801.127 (HA09)
/PlayStation 2 - MAIN/BIOS/A10: RN1303.8 (R1.2), U1703.7 (A9), U1801.126 (HA10)
/PlayStation 2 - MAIN/BIOS/A11: RN1302.5 (R4.2), U1703.6 (A10), U1801.125 (HA11)
/PlayStation 2 - MAIN/BIOS/A12: RN1301.1 (R1.1), U1703.5 (A11), U1801.122 (HA12)
/PlayStation 2 - MAIN/BIOS/A13: RN1302.6 (R3.2), U1703.4 (A12), U1801.121 (HA13)
/PlayStation 2 - MAIN/BIOS/A14: RN1302.7 (R2.2), U1703.3 (A13), U1801.120 (HA14)
/PlayStation 2 - MAIN/BIOS/A15: RN1302.8 (R1.2), U1703.2 (A14), U1801.119 (HA15)
/PlayStation 2 - MAIN/BIOS/A16: U901.AK32 (SA16), U1703.1 (A15)
/PlayStation 2 - MAIN/BIOS/A17: U901.AK33 (SA17), U1703.48 (A16)
/PlayStation 2 - MAIN/BIOS/A18: U901.AJ32 (SA18), U1703.17 (A17)
/PlayStation 2 - MAIN/BIOS/A19: U901.AJ34 (SA19), U1703.16 (A18)
/PlayStation 2 - MAIN/BIOS/A20: U901.AL34 (SA20), U1703.9 (A19)
/PlayStation 2 - MAIN/BIOS/A21: U901.AL33 (SA21), U1703.10 (A20)
/PlayStation 2 - MAIN/BIOS/A22: TP1701.1, U901.AM34 (SA22)
/PlayStation 2 - MAIN/BIOS/BCKO: U901.J32 (SPUBCKI), U1801.181 (BCKO)
/PlayStation 2 - MAIN/BIOS/D0: RN1308.4 (R4.1), U1703.29 (D0), U1801.164 (HDB00)
/PlayStation 2 - MAIN/BIOS/D1: RN1308.3 (R3.1), U1703.31 (D1), U1801.163 (HDB01)
/PlayStation 2 - MAIN/BIOS/D2: RN1308.2 (R2.1), U1703.33 (D2), U1801.162 (HDB02)
/PlayStation 2 - MAIN/BIOS/D3: RN1308.1 (R1.1), U1703.35 (D3), U1801.161 (HDB03)
/PlayStation 2 - MAIN/BIOS/D4: RN1306.4 (R4.1), U1703.38 (D4), U1801.158 (HDB04)
/PlayStation 2 - MAIN/BIOS/D5: RN1307.1 (R1.1), U1703.40 (D5), U1801.157 (HDB05)
/PlayStation 2 - MAIN/BIOS/D6: RN1307.2 (R2.1), U1703.42 (D6), U1801.156 (HDB06)
/PlayStation 2 - MAIN/BIOS/D7: RN1307.3 (R3.1), U1703.44 (D7), U1801.155 (HDB07)
/PlayStation 2 - MAIN/BIOS/D8: RN1306.3 (R3.1), U1703.30 (D8), U1801.152 (HDB08)
/PlayStation 2 - MAIN/BIOS/D9: RN1306.2 (R2.1), U1703.32 (D9), U1801.151 (HDB09)
/PlayStation 2 - MAIN/BIOS/D10: RN1307.4 (R4.1), U1703.34 (D10), U1801.150 (HDB10)
/PlayStation 2 - MAIN/BIOS/D11: RN1306.1 (R1.1), U1703.36 (D11), U1801.149 (HDB11)
/PlayStation 2 - MAIN/BIOS/D12: RN1305.4 (R4.1), U1703.39 (D12), U1801.146 (HDB12)
/PlayStation 2 - MAIN/BIOS/D13: RN1305.3 (R3.1), U1703.41 (D13), U1801.145 (HDB13)
/PlayStation 2 - MAIN/BIOS/D14: RN1305.2 (R2.1), U1703.43 (D14), U1801.144 (HDB14)
/PlayStation 2 - MAIN/BIOS/D15: R1702.2, RN1305.1 (R1.1), U1801.143 (HDB15)
/PlayStation 2 - MAIN/BIOS/DATO: U901.H32 (SPUDATI), U1801.182 (DATO)
/PlayStation 2 - MAIN/BIOS/DOUT: U901.H33 (SPUDIN), U1801.183 (DOUT)
/PlayStation 2 - MAIN/BIOS/DSP_TRST: C1301.1, R1305.2, U1801.72 (~TRST), U1801.76 (~RST)
/PlayStation 2 - MAIN/BIOS/HACK: U901.AH33 (HACK), U1801.174 (HACK)
/PlayStation 2 - MAIN/BIOS/HDRQ: R1306.1, U1801.173 (HDRQ)
/PlayStation 2 - MAIN/BIOS/LRCO: U901.J31 (SPULRCKI), U1801.180 (LRCO)
/PlayStation 2 - MAIN/BIOS/SCLK0: C1302.1, R1301.1, U1801.179 (SCLK0)
/PlayStation 2 - MAIN/BIOS/SCLK1: R1302.1, U1801.176 (SCLK1)
/PlayStation 2 - MAIN/BIOS/~BYTE: U1701.4, U1702.1, U1703.47 (~BYTE)
/PlayStation 2 - MAIN/BIOS/~CE1: TP1702.1, U901.AH31 (~CS1), U1702.2, U1703.13 (A21)
/PlayStation 2 - MAIN/BIOS/~CE2: TP1704.1, U901.AK34 (~CS2), U1701.1
/PlayStation 2 - MAIN/BIOS/~CE: U1702.4, U1703.26 (~CE)
/PlayStation 2 - MAIN/BIOS/~HINT: U901.AH32 (~HINT), U1801.175 (~HINT)
/PlayStation 2 - MAIN/BIOS/~OE: RN1309.6 (R3.2), U1703.28 (~OE)
/PlayStation 2 - MAIN/BIOS/~PPCCS: TP1703.1, U901.AJ31 (~PPCCS), U1701.2
/PlayStation 2 - MAIN/BIOS/~XHCS: R1303.1, TP1901.1, U1801.169 (~XHCS)
/PlayStation 2 - MAIN/BIOS/~XHRD: RN1309.5 (R4.2), U1801.168 (~XHRD)
/PlayStation 2 - MAIN/BIOS/~XHWR: RN1309.8 (R1.2), U1801.167 (~XHWR)
/PlayStation 2 - MAIN/CLK_EE: R801.2, U901.L34 (CLOCK_IC_15)
/PlayStation 2 - MAIN/CLK_ETH: U801.6 (CLKOUT_ETH_PIN2), U2001.2 (CLOCK_IC_6)
/PlayStation 2 - MAIN/CLK_GS: R802.2, U2201.M1 (CLOCK_IC_9)
/PlayStation 2 - MAIN/CLOCK: R2308.2, U2601.F16 (GPIOR_123_CLK12_CDI20)
/PlayStation 2 - MAIN/DAC_RST: TP2904.1, U901.C33 (DAC_RESET), U2601.H16 (GPIOR_130_CTRL9)
/PlayStation 2 - MAIN/DAC_SCL: R1201.2, TP2901.1, U901.D34 (DAC_SCL), U2601.G15 (GPIOR_124_CLK11)
/PlayStation 2 - MAIN/DAC_SDA: R1202.2, TP2903.1, U901.D33 (DAC_SDA), U2601.H15 (GPIOR_129_CTRL10)
/PlayStation 2 - MAIN/DSP/MCA0: U1401.D6 (MCA0), U1801.116 (MCA0)
/PlayStation 2 - MAIN/DSP/MCA1: U1401.A5 (MCA1), U1801.115 (MCA1)
/PlayStation 2 - MAIN/DSP/MCA2: U1401.C5 (MCA2), U1801.114 (MCA2)
/PlayStation 2 - MAIN/DSP/MCA3: U1401.A4 (MCA3), U1801.113 (MCA3)
/PlayStation 2 - MAIN/DSP/MCA4: U1401.B4 (MCA4), U1801.112 (MCA4)
/PlayStation 2 - MAIN/DSP/MCA5: U1401.A3 (MCA5), U1801.111 (MCA5)
/PlayStation 2 - MAIN/DSP/MCA6: U1401.B3 (MCA6), U1801.110 (MCA6)
/PlayStation 2 - MAIN/DSP/MCA7: U1401.A2 (MCA7), U1801.109 (MCA7)
/PlayStation 2 - MAIN/DSP/MCA8: U1401.C4 (MCA8), U1801.108 (MCA8)
/PlayStation 2 - MAIN/DSP/MCD0: U1401.G1 (MCD0), U1801.86 (MCD0)
/PlayStation 2 - MAIN/DSP/MCD1: U1401.H1 (MCD1), U1801.85 (MCD1)
/PlayStation 2 - MAIN/DSP/MCD2: U1401.J1 (MCD2), U1801.84 (MCD2)
/PlayStation 2 - MAIN/DSP/MCD3: U1401.H2 (MCD3), U1801.83 (MCD3)
/PlayStation 2 - MAIN/DSP/MCD4: U1401.G4 (MCD4), U1801.82 (MCD4)
/PlayStation 2 - MAIN/DSP/MCD5: U1401.K1 (MCD5), U1801.81 (MCD5)
/PlayStation 2 - MAIN/DSP/MCD6: U1401.L1 (MCD6), U1801.80 (MCD6)
/PlayStation 2 - MAIN/DSP/MCD7: U1401.J2 (MCD7), U1801.79 (MCD7)
/PlayStation 2 - MAIN/DSP/SSTP: R1501.2, U1401.E10 (LIMIT_SW)
/PlayStation 2 - MAIN/DSP/~INT1: R1503.2, U1401.K2 (~INT_3098), U1801.78 (~INT1)
/PlayStation 2 - MAIN/DSP/~MCCS: U1401.F1 (~CS_3098), U1801.89 (~MCCS)
/PlayStation 2 - MAIN/DSP/~MCRD: U1401.A7 (~MCRD), U1801.90 (~MCRD)
/PlayStation 2 - MAIN/DSP/~MCWR: U1401.A8 (~MCWR), U1801.91 (~MCWR)
/PlayStation 2 - MAIN/EE Front IO/GAMEPAD1_?: R2406.2, TP2401.1, U901.AP6 (GAMEPAD1_?)
/PlayStation 2 - MAIN/EE Front IO/GAMEPAD1_ACK: C2402.1, R2405.2, RN2401.8 (R1.2), U901.AN6 (GAMEPAD1_ACK)
/PlayStation 2 - MAIN/EE Front IO/GAMEPAD1_ATT: RN2402.7 (R2.2), U901.AN9 (GAMEPAD1_ATT)
/PlayStation 2 - MAIN/EE Front IO/GAMEPAD1_CLK: RN2402.8 (R1.2), U901.AP8 (GAMEPAD1_CLK)
/PlayStation 2 - MAIN/EE Front IO/GAMEPAD1_CMD: RN2404.8 (R1.2), U901.AP10 (GAMEPAD1_CMD)
/PlayStation 2 - MAIN/EE Front IO/GAMEPAD1_DAT: RN2404.7 (R2.2), U901.AN11 (GAMEPAD1_DAT)
/PlayStation 2 - MAIN/EE Front IO/GAMEPAD2_?: R2401.2, TP2412.1, U901.AN12 (GAMEPAD2_?)
/PlayStation 2 - MAIN/EE Front IO/GAMEPAD2_ACK: R2403.2, TP2410.1, U901.AP11 (GAMEPAD2_ACK)
/PlayStation 2 - MAIN/EE Front IO/GAMEPAD2_ATT: TP2411.1, U901.AP14 (GAMEPAD2_ATT)
/PlayStation 2 - MAIN/EE Front IO/GAMEPAD2_CLK: TP2409.1, U901.AN14 (GAMEPAD2_CLK)
/PlayStation 2 - MAIN/EE Front IO/GAMEPAD2_CMD: TP2407.1, U901.AN16 (GAMEPAD2_CMD)
/PlayStation 2 - MAIN/EE Front IO/GAMEPAD2_DAT: R2402.2, TP2408.1, U901.AP16 (GAMEPAD2_DAT)
/PlayStation 2 - MAIN/EE Front IO/MEMCARD1_ACK: R2408.2, RN2401.7 (R2.2), U901.AN7 (MEMCARD1_ACK)
/PlayStation 2 - MAIN/EE Front IO/MEMCARD1_ATT: RN2401.5 (R4.2), U901.AN8 (MEMCARD1_ATT)
/PlayStation 2 - MAIN/EE Front IO/MEMCARD1_CLK: RN2401.6 (R3.2), U901.AP7 (MEMCARD1_CLK)
/PlayStation 2 - MAIN/EE Front IO/MEMCARD1_CMD: RN2402.6 (R3.2), U901.AP9 (MEMCARD1_CMD)
/PlayStation 2 - MAIN/EE Front IO/MEMCARD1_DAT: R2411.2, RN2402.5 (R4.2), U901.AN10 (MEMCARD1_DAT)
/PlayStation 2 - MAIN/EE Front IO/MEMCARD2_ACK: R2409.2, RN2404.6 (R3.2), U901.AP12 (MEMCARD2_ACK)
/PlayStation 2 - MAIN/EE Front IO/MEMCARD2_ATT: RN2403.8 (R1.2), U901.AP13 (MEMCARD2_ATT)
/PlayStation 2 - MAIN/EE Front IO/MEMCARD2_CLK: RN2404.5 (R4.2), U901.AN13 (MEMCARD2_CLK)
/PlayStation 2 - MAIN/EE Front IO/MEMCARD2_CMD: RN2403.7 (R2.2), U901.AN15 (MEMCARD2_CMD)
/PlayStation 2 - MAIN/EE Front IO/MEMCARD2_DAT: R2412.2, RN2403.6 (R3.2), U901.AP15 (MEMCARD2_DAT)
/PlayStation 2 - MAIN/GCONT: TP2308.1, U2201.L2 (GCONT)
/PlayStation 2 - MAIN/GS/CLOCK_O: R2308.1, TP2307.1, U2201.D1 (PXL_CLOCK)
/PlayStation 2 - MAIN/GS/CSYNC_O: TP2306.1, U2201.C5 (CSYNC)
/PlayStation 2 - MAIN/GS/GS_A15: U901.A32 (GS_A15), U2201.A15 (EE_A32)
/PlayStation 2 - MAIN/GS/GS_A16: U901.A31 (GS_A16), U2201.A16 (EE_A31)
/PlayStation 2 - MAIN/GS/GS_A18: RN2310.3 (R3.1), U901.A29 (GS_A18)
/PlayStation 2 - MAIN/GS/GS_A19: RN2310.1 (R1.1), U901.A28 (GS_A19)
/PlayStation 2 - MAIN/GS/GS_A20: RN2311.3 (R3.1), U901.A27 (GS_A20)
/PlayStation 2 - MAIN/GS/GS_AA16: U901.B4 (GS_AA16), U2201.AA16 (EE_B4)
/PlayStation 2 - MAIN/GS/GS_AA17: R2305.2, U901.B5 (GS_AA17)
/PlayStation 2 - MAIN/GS/GS_AA19: RN2318.6 (R3.2), U901.B7 (GS_AA19)
/PlayStation 2 - MAIN/GS/GS_AA20: R2301.1, U901.B8 (GS_AA20)
/PlayStation 2 - MAIN/GS/GS_AB13: R2306.2, U901.C1 (GS_AB13)
/PlayStation 2 - MAIN/GS/GS_AB15: U901.A3 (GS_AB15), U2201.AB15 (EE_A3)
/PlayStation 2 - MAIN/GS/GS_AB16: U901.A4 (GS_AB16), U2201.AB16 (EE_A4)
/PlayStation 2 - MAIN/GS/GS_AB17: R2304.2, U901.A5 (GS_AB17)
/PlayStation 2 - MAIN/GS/GS_AB18: U901.A6 (GS_AB18), U2201.AB18 (EE_A6)
/PlayStation 2 - MAIN/GS/GS_AB19: RN2318.7 (R2.2), U901.A7 (GS_AB19)
/PlayStation 2 - MAIN/GS/GS_AB20: RN2318.8 (R1.2), U901.A8 (GS_AB20)
/PlayStation 2 - MAIN/GS/GS_B17: RN2310.4 (R4.1), U901.B30 (GS_B17)
/PlayStation 2 - MAIN/GS/GS_B18: RN2310.2 (R2.1), U901.B29 (GS_B18)
/PlayStation 2 - MAIN/GS/GS_B19: RN2311.4 (R4.1), U901.B28 (GS_B19)
/PlayStation 2 - MAIN/GS/GS_B20: RN2311.2 (R2.1), U901.B27 (GS_B20)
/PlayStation 2 - MAIN/GS/GS_C17: RN2301.5 (R4.2), U901.C30 (GS_C17)
/PlayStation 2 - MAIN/GS/GS_C18: RN2301.7 (R2.2), U901.C29 (GS_C18)
/PlayStation 2 - MAIN/GS/GS_C19: RN2302.5 (R4.2), U901.C28 (GS_C19)
/PlayStation 2 - MAIN/GS/GS_C21: RN2312.4 (R4.1), U901.B26 (GS_C21)
/PlayStation 2 - MAIN/GS/GS_C22: RN2311.1 (R1.1), U901.A26 (GS_C22)
/PlayStation 2 - MAIN/GS/GS_D17: RN2301.6 (R3.2), U901.D30 (GS_D17)
/PlayStation 2 - MAIN/GS/GS_D18: RN2301.8 (R1.2), U901.D29 (GS_D18)
/PlayStation 2 - MAIN/GS/GS_D20: RN2302.6 (R3.2), U901.C25 (GS_D20)
/PlayStation 2 - MAIN/GS/GS_D21: RN2312.2 (R2.1), U901.B25 (GS_D21)
/PlayStation 2 - MAIN/GS/GS_D22: RN2312.3 (R3.1), U901.A25 (GS_D22)
/PlayStation 2 - MAIN/GS/GS_E19: RN2302.7 (R2.2), U901.D24 (GS_E19)
/PlayStation 2 - MAIN/GS/GS_E20: RN2302.8 (R1.2), U901.C24 (GS_E20)
/PlayStation 2 - MAIN/GS/GS_E22: RN2312.1 (R1.1), U901.A24 (GS_E22)
/PlayStation 2 - MAIN/GS/GS_F19: RN2303.5 (R4.2), U901.D23 (GS_F19)
/PlayStation 2 - MAIN/GS/GS_F20: RN2303.6 (R3.2), U901.C23 (GS_F20)
/PlayStation 2 - MAIN/GS/GS_F21: RN2313.3 (R3.1), U901.B23 (GS_F21)
/PlayStation 2 - MAIN/GS/GS_F22: RN2313.4 (R4.1), U901.A23 (GS_F22)
/PlayStation 2 - MAIN/GS/GS_G19: RN2303.7 (R2.2), U901.D22 (GS_G19)
/PlayStation 2 - MAIN/GS/GS_G20: RN2303.8 (R1.2), U901.C22 (GS_G20)
/PlayStation 2 - MAIN/GS/GS_G21: RN2313.1 (R1.1), U901.B22 (GS_G21)
/PlayStation 2 - MAIN/GS/GS_G22: RN2313.2 (R2.1), U901.A22 (GS_G22)
/PlayStation 2 - MAIN/GS/GS_H19: RN2304.5 (R4.2), U901.D21 (GS_H19)
/PlayStation 2 - MAIN/GS/GS_H20: RN2304.8 (R1.2), U901.C20 (GS_J20)
/PlayStation 2 - MAIN/GS/GS_H21: RN2304.6 (R3.2), U901.B21 (GS_H21)
/PlayStation 2 - MAIN/GS/GS_H22: RN2314.4 (R4.1), U901.A21 (GS_H22)
/PlayStation 2 - MAIN/GS/GS_J19: RN2304.7 (R2.2), U901.D20 (GS_J19)
/PlayStation 2 - MAIN/GS/GS_J21: RN2314.2 (R2.1), U901.B20 (GS_J21)
/PlayStation 2 - MAIN/GS/GS_J22: RN2314.3 (R3.1), U901.A20 (GS_J22)
/PlayStation 2 - MAIN/GS/GS_K19: RN2305.5 (R4.2), U901.D19 (GS_K19)
/PlayStation 2 - MAIN/GS/GS_K20: RN2305.6 (R3.2), U901.C19 (GS_K20)
/PlayStation 2 - MAIN/GS/GS_K21: RN2314.1 (R1.1), U901.B19 (GS_K21)
/PlayStation 2 - MAIN/GS/GS_L19: RN2305.7 (R2.2), U901.D18 (GS_L19)
/PlayStation 2 - MAIN/GS/GS_L20: RN2305.8 (R1.2), U901.C18 (GS_L20)
/PlayStation 2 - MAIN/GS/GS_L22: R2302.2, U901.A18 (GS_L22)
/PlayStation 2 - MAIN/GS/GS_M20: RN2306.6 (R3.2), U901.C17 (GS_M20)
/PlayStation 2 - MAIN/GS/GS_M21: RN2306.5 (R4.2), U901.B17 (GS_M21)
/PlayStation 2 - MAIN/GS/GS_N19: RN2306.8 (R1.2), U901.D16 (GS_N19)
/PlayStation 2 - MAIN/GS/GS_N20: RN2306.7 (R2.2), U901.C16 (GS_N20)
/PlayStation 2 - MAIN/GS/GS_N22: R2303.2, U901.A16 (GS_N22)
/PlayStation 2 - MAIN/GS/GS_P19: RN2307.6 (R3.2), U901.D15 (GS_P19)
/PlayStation 2 - MAIN/GS/GS_P20: RN2307.5 (R4.2), U901.C15 (GS_P20)
/PlayStation 2 - MAIN/GS/GS_P21: RN2315.4 (R4.1), U901.B15 (GS_P21)
/PlayStation 2 - MAIN/GS/GS_R19: RN2307.7 (R2.2), U901.D14 (GS_R19)
/PlayStation 2 - MAIN/GS/GS_R21: RN2315.2 (R2.1), U901.B14 (GS_R21)
/PlayStation 2 - MAIN/GS/GS_R22: RN2315.3 (R3.1), U901.A14 (GS_R22)
/PlayStation 2 - MAIN/GS/GS_T19: RN2308.5 (R4.2), U901.D13 (GS_T19)
/PlayStation 2 - MAIN/GS/GS_T20: RN2307.8 (R1.2), U901.C13 (GS_T20)
/PlayStation 2 - MAIN/GS/GS_T21: RN2316.8 (R1.2), U901.B13 (GS_T21)
/PlayStation 2 - MAIN/GS/GS_T22: RN2315.1 (R1.1), U901.A13 (GS_T22)
/PlayStation 2 - MAIN/GS/GS_U19: RN2308.7 (R2.2), U901.D12 (GS_U19)
/PlayStation 2 - MAIN/GS/GS_U20: RN2308.6 (R3.2), U901.C12 (GS_U20)
/PlayStation 2 - MAIN/GS/GS_U21: RN2316.6 (R3.2), U901.B12 (GS_U21)
/PlayStation 2 - MAIN/GS/GS_U22: RN2316.7 (R2.2), U901.A12 (GS_U22)
/PlayStation 2 - MAIN/GS/GS_V19: RN2309.5 (R4.2), U901.D11 (GS_V19)
/PlayStation 2 - MAIN/GS/GS_V20: RN2308.8 (R1.2), U901.C11 (GS_V20)
/PlayStation 2 - MAIN/GS/GS_V22: RN2316.5 (R4.2), U901.A11 (GS_V22)
/PlayStation 2 - MAIN/GS/GS_W17: U901.D5 (GS_W17), U2201.W17 (EE_D5)
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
